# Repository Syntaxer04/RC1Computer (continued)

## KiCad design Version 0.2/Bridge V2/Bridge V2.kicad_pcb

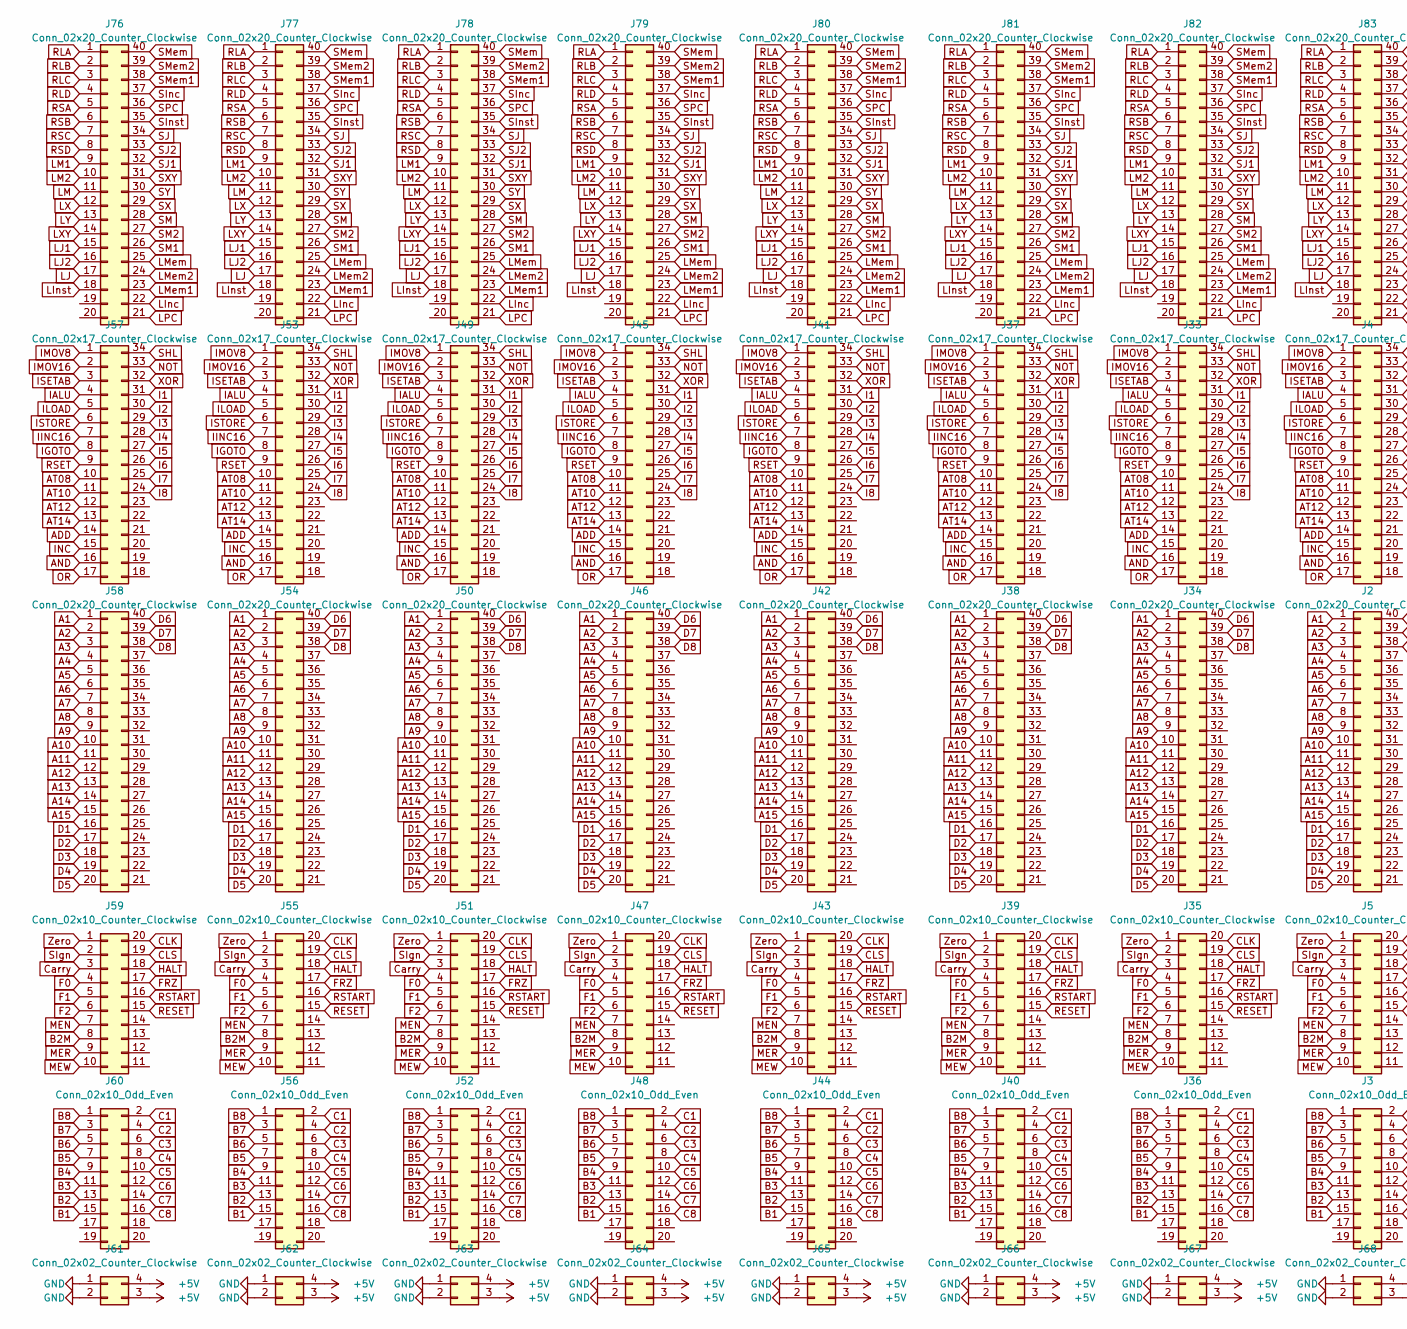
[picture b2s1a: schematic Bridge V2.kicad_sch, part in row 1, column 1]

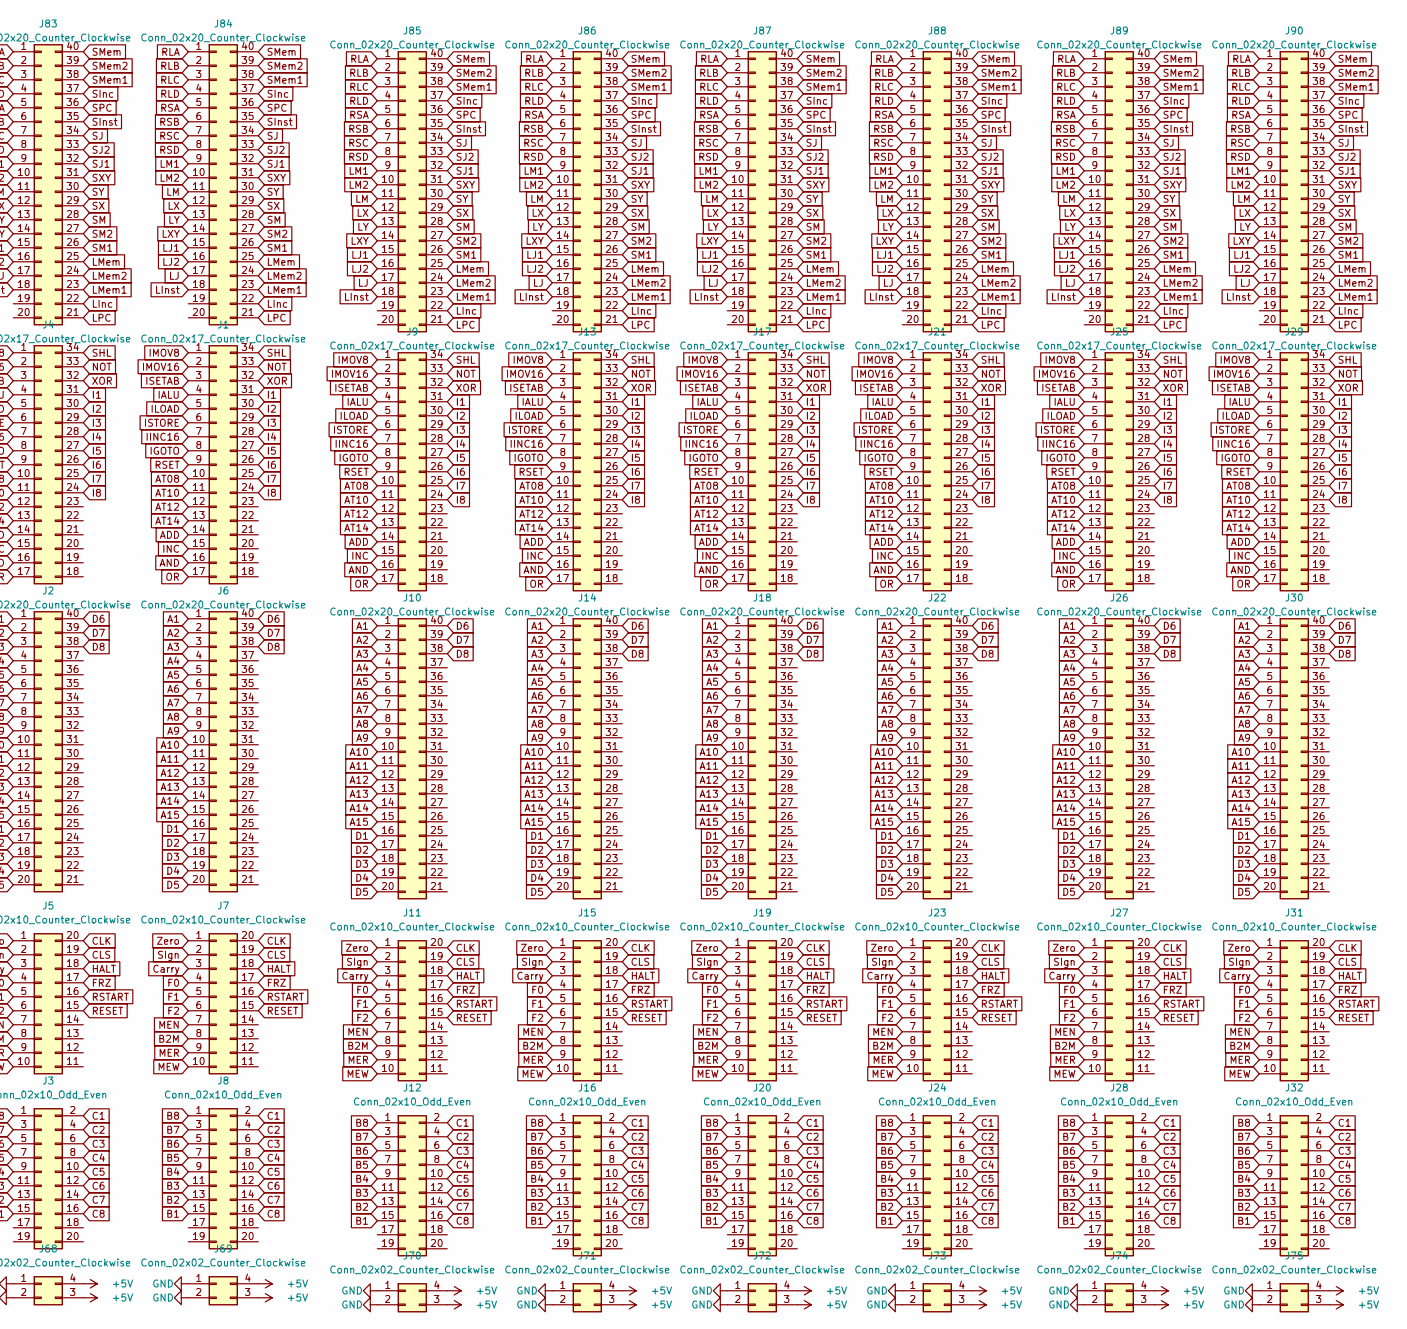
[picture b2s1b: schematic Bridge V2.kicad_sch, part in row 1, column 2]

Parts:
J1, J4, J9, J13, J17, J21, J25, J29, J33, J37, J41, J45, J49, J53, J57: Conn_02x17_Counter_Clockwise; PinSocket_2x17_P2.54mm_Vertical
J2, J6, J10, J14, J18, J22, J26, J30, J34, J38, J42, J46, J50, J54, J58, J76, J77, J78, J79, J80, J81, J82, J83, J84, J85, J86, J87, J88, J89, J90: Conn_02x20_Counter_Clockwise; PinSocket_2x20_P2.54mm_Vertical
J3, J8, J12, J16, J20, J24, J28, J32, J36, J40, J44, J48, J52, J56, J60: Conn_02x10_Odd_Even; PinSocket_2x10_P2.54mm_Vertical
J5, J7, J11, J15, J19, J23, J27, J31, J35, J39, J43, J47, J51, J55, J59: Conn_02x10_Counter_Clockwise; PinSocket_2x10_P2.54mm_Vertical
J61, J62, J63, J64, J65, J66, J67, J68, J69, J70, J71, J72, J73, J74, J75: Conn_02x02_Counter_Clockwise; PinSocket_2x02_P2.54mm_Vertical

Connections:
+5V: J61.3, J61.4, J62.3, J62.4, J63.3, J63.4, J64.3, J64.4, J65.3, J65.4, J66.3, J66.4, J67.3, J67.4, J68.3, J68.4, J69.3, J69.4, J70.3, J70.4, J71.3, J71.4, J72.3, J72.4, J73.3, J73.4, J74.3, J74.4, J75.3, J75.4
A1: J2.1, J6.1, J10.1, J14.1, J18.1, J22.1, J26.1, J30.1, J34.1, J38.1, J42.1, J46.1, J50.1, J54.1, J58.1
A2: J2.2, J6.2, J10.2, J14.2, J18.2, J22.2, J26.2, J30.2, J34.2, J38.2, J42.2, J46.2, J50.2, J54.2, J58.2
A3: J2.3, J6.3, J10.3, J14.3, J18.3, J22.3, J26.3, J30.3, J34.3, J38.3, J42.3, J46.3, J50.3, J54.3, J58.3
A4: J2.4, J6.4, J10.4, J14.4, J18.4, J22.4, J26.4, J30.4, J34.4, J38.4, J42.4, J46.4, J50.4, J54.4, J58.4
A5: J2.5, J6.5, J10.5, J14.5, J18.5, J22.5, J26.5, J30.5, J34.5, J38.5, J42.5, J46.5, J50.5, J54.5, J58.5
A6: J2.6, J6.6, J10.6, J14.6, J18.6, J22.6, J26.6, J30.6, J34.6, J38.6, J42.6, J46.6, J50.6, J54.6, J58.6
A7: J2.7, J6.7, J10.7, J14.7, J18.7, J22.7, J26.7, J30.7, J34.7, J38.7, J42.7, J46.7, J50.7, J54.7, J58.7
A8: J2.8, J6.8, J10.8, J14.8, J18.8, J22.8, J26.8, J30.8, J34.8, J38.8, J42.8, J46.8, J50.8, J54.8, J58.8
A9: J2.9, J6.9, J10.9, J14.9, J18.9, J22.9, J26.9, J30.9, J34.9, J38.9, J42.9, J46.9, J50.9, J54.9, J58.9
A10: J2.10, J6.10, J10.10, J14.10, J18.10, J22.10, J26.10, J30.10, J34.10, J38.10, J42.10, J46.10, J50.10, J54.10, J58.10
A11: J2.11, J6.11, J10.11, J14.11, J18.11, J22.11, J26.11, J30.11, J34.11, J38.11, J42.11, J46.11, J50.11, J54.11, J58.11
A12: J2.12, J6.12, J10.12, J14.12, J18.12, J22.12, J26.12, J30.12, J34.12, J38.12, J42.12, J46.12, J50.12, J54.12, J58.12
A13: J2.13, J6.13, J10.13, J14.13, J18.13, J22.13, J26.13, J30.13, J34.13, J38.13, J42.13, J46.13, J50.13, J54.13, J58.13
A14: J2.14, J6.14, J10.14, J14.14, J18.14, J22.14, J26.14, J30.14, J34.14, J38.14, J42.14, J46.14, J50.14, J54.14, J58.14
A15: J2.15, J6.15, J10.15, J14.15, J18.15, J22.15, J26.15, J30.15, J34.15, J38.15, J42.15, J46.15, J50.15, J54.15, J58.15
ADD: J1.14, J4.14, J9.14, J13.14, J17.14, J21.14, J25.14, J29.14, J33.14, J37.14, J41.14, J45.14, J49.14, J53.14, J57.14
AND: J1.16, J4.16, J9.16, J13.16, J17.16, J21.16, J25.16, J29.16, J33.16, J37.16, J41.16, J45.16, J49.16, J53.16, J57.16
AT08: J1.10, J4.10, J9.10, J13.10, J17.10, J21.10, J25.10, J29.10, J33.10, J37.10, J41.10, J45.10, J49.10, J53.10, J57.10
AT10: J1.11, J4.11, J9.11, J13.11, J17.11, J21.11, J25.11, J29.11, J33.11, J37.11, J41.11, J45.11, J49.11, J53.11, J57.11
AT12: J1.12, J4.12, J9.12, J13.12, J17.12, J21.12, J25.12, J29.12, J33.12, J37.12, J41.12, J45.12, J49.12, J53.12, J57.12
AT14: J1.13, J4.13, J9.13, J13.13, J17.13, J21.13, J25.13, J29.13, J33.13, J37.13, J41.13, J45.13, J49.13, J53.13, J57.13
B1: J3.15, J8.15, J12.15, J16.15, J20.15, J24.15, J28.15, J32.15, J36.15, J40.15, J44.15, J48.15, J52.15, J56.15, J60.15
B2: J3.13, J8.13, J12.13, J16.13, J20.13, J24.13, J28.13, J32.13, J36.13, J40.13, J44.13, J48.13, J52.13, J56.13, J60.13
B2M: J5.8, J7.8, J11.8, J15.8, J19.8, J23.8, J27.8, J31.8, J35.8, J39.8, J43.8, J47.8, J51.8, J55.8, J59.8
B3: J3.11, J8.11, J12.11, J16.11, J20.11, J24.11, J28.11, J32.11, J36.11, J40.11, J44.11, J48.11, J52.11, J56.11, J60.11
B4: J3.9, J8.9, J12.9, J16.9, J20.9, J24.9, J28.9, J32.9, J36.9, J40.9, J44.9, J48.9, J52.9, J56.9, J60.9
B5: J3.7, J8.7, J12.7, J16.7, J20.7, J24.7, J28.7, J32.7, J36.7, J40.7, J44.7, J48.7, J52.7, J56.7, J60.7
B6: J3.5, J8.5, J12.5, J16.5, J20.5, J24.5, J28.5, J32.5, J36.5, J40.5, J44.5, J48.5, J52.5, J56.5, J60.5
B7: J3.3, J8.3, J12.3, J16.3, J20.3, J24.3, J28.3, J32.3, J36.3, J40.3, J44.3, J48.3, J52.3, J56.3, J60.3
B8: J3.1, J8.1, J12.1, J16.1, J20.1, J24.1, J28.1, J32.1, J36.1, J40.1, J44.1, J48.1, J52.1, J56.1, J60.1
C1: J3.2, J8.2, J12.2, J16.2, J20.2, J24.2, J28.2, J32.2, J36.2, J40.2, J44.2, J48.2, J52.2, J56.2, J60.2
C2: J3.4, J8.4, J12.4, J16.4, J20.4, J24.4, J28.4, J32.4, J36.4, J40.4, J44.4, J48.4, J52.4, J56.4, J60.4
C3: J3.6, J8.6, J12.6, J16.6, J20.6, J24.6, J28.6, J32.6, J36.6, J40.6, J44.6, J48.6, J52.6, J56.6, J60.6
C4: J3.8, J8.8, J12.8, J16.8, J20.8, J24.8, J28.8, J32.8, J36.8, J40.8, J44.8, J48.8, J52.8, J56.8, J60.8
C5: J3.10, J8.10, J12.10, J16.10, J20.10, J24.10, J28.10, J32.10, J36.10, J40.10, J44.10, J48.10, J52.10, J56.10, J60.10
C6: J3.12, J8.12, J12.12, J16.12, J20.12, J24.12, J28.12, J32.12, J36.12, J40.12, J44.12, J48.12, J52.12, J56.12, J60.12
C7: J3.14, J8.14, J12.14, J16.14, J20.14, J24.14, J28.14, J32.14, J36.14, J40.14, J44.14, J48.14, J52.14, J56.14, J60.14
C8: J3.16, J8.16, J12.16, J16.16, J20.16, J24.16, J28.16, J32.16, J36.16, J40.16, J44.16, J48.16, J52.16, J56.16, J60.16
CLK: J5.20, J7.20, J11.20, J15.20, J19.20, J23.20, J27.20, J31.20, J35.20, J39.20, J43.20, J47.20, J51.20, J55.20, J59.20
CLS: J5.19, J7.19, J11.19, J15.19, J19.19, J23.19, J27.19, J31.19, J35.19, J39.19, J43.19, J47.19, J51.19, J55.19, J59.19
Carry: J5.3, J7.3, J11.3, J15.3, J19.3, J23.3, J27.3, J31.3, J35.3, J39.3, J43.3, J47.3, J51.3, J55.3, J59.3
D1: J2.16, J6.16, J10.16, J14.16, J18.16, J22.16, J26.16, J30.16, J34.16, J38.16, J42.16, J46.16, J50.16, J54.16, J58.16
D2: J2.17, J6.17, J10.17, J14.17, J18.17, J22.17, J26.17, J30.17, J34.17, J38.17, J42.17, J46.17, J50.17, J54.17, J58.17
D3: J2.18, J6.18, J10.18, J14.18, J18.18, J22.18, J26.18, J30.18, J34.18, J38.18, J42.18, J46.18, J50.18, J54.18, J58.18
D4: J2.19, J6.19, J10.19, J14.19, J18.19, J22.19, J26.19, J30.19, J34.19, J38.19, J42.19, J46.19, J50.19, J54.19, J58.19
D5: J2.20, J6.20, J10.20, J14.20, J18.20, J22.20, J26.20, J30.20, J34.20, J38.20, J42.20, J46.20, J50.20, J54.20, J58.20
D6: J2.40, J6.40, J10.40, J14.40, J18.40, J22.40, J26.40, J30.40, J34.40, J38.40, J42.40, J46.40, J50.40, J54.40, J58.40
D7: J2.39, J6.39, J10.39, J14.39, J18.39, J22.39, J26.39, J30.39, J34.39, J38.39, J42.39, J46.39, J50.39, J54.39, J58.39
D8: J2.38, J6.38, J10.38, J14.38, J18.38, J22.38, J26.38, J30.38, J34.38, J38.38, J42.38, J46.38, J50.38, J54.38, J58.38
F0: J5.4, J7.4, J11.4, J15.4, J19.4, J23.4, J27.4, J31.4, J35.4, J39.4, J43.4, J47.4, J51.4, J55.4, J59.4
F1: J5.5, J7.5, J11.5, J15.5, J19.5, J23.5, J27.5, J31.5, J35.5, J39.5, J43.5, J47.5, J51.5, J55.5, J59.5
F2: J5.6, J7.6, J11.6, J15.6, J19.6, J23.6, J27.6, J31.6, J35.6, J39.6, J43.6, J47.6, J51.6, J55.6, J59.6
FRZ: J5.17, J7.17, J11.17, J15.17, J19.17, J23.17, J27.17, J31.17, J35.17, J39.17, J43.17, J47.17, J51.17, J55.17, J59.17
GND: J61.1, J61.2, J62.1, J62.2, J63.1, J63.2, J64.1, J64.2, J65.1, J65.2, J66.1, J66.2, J67.1, J67.2, J68.1, J68.2, J69.1, J69.2, J70.1, J70.2, J71.1, J71.2, J72.1, J72.2, J73.1, J73.2, J74.1, J74.2, J75.1, J75.2
HALT: J5.18, J7.18, J11.18, J15.18, J19.18, J23.18, J27.18, J31.18, J35.18, J39.18, J43.18, J47.18, J51.18, J55.18, J59.18
I1: J1.31, J4.31, J9.31, J13.31, J17.31, J21.31, J25.31, J29.31, J33.31, J37.31, J41.31, J45.31, J49.31, J53.31, J57.31
I2: J1.30, J4.30, J9.30, J13.30, J17.30, J21.30, J25.30, J29.30, J33.30, J37.30, J41.30, J45.30, J49.30, J53.30, J57.30
I3: J1.29, J4.29, J9.29, J13.29, J17.29, J21.29, J25.29, J29.29, J33.29, J37.29, J41.29, J45.29, J49.29, J53.29, J57.29
I4: J1.28, J4.28, J9.28, J13.28, J17.28, J21.28, J25.28, J29.28, J33.28, J37.28, J41.28, J45.28, J49.28, J53.28, J57.28
I5: J1.27, J4.27, J9.27, J13.27, J17.27, J21.27, J25.27, J29.27, J33.27, J37.27, J41.27, J45.27, J49.27, J53.27, J57.27
I6: J1.26, J4.26, J9.26, J13.26, J17.26, J21.26, J25.26, J29.26, J33.26, J37.26, J41.26, J45.26, J49.26, J53.26, J57.26
I7: J1.25, J4.25, J9.25, J13.25, J17.25, J21.25, J25.25, J29.25, J33.25, J37.25, J41.25, J45.25, J49.25, J53.25, J57.25
I8: J1.24, J4.24, J9.24, J13.24, J17.24, J21.24, J25.24, J29.24, J33.24, J37.24, J41.24, J45.24, J49.24, J53.24, J57.24
IALU: J1.4, J4.4, J9.4, J13.4, J17.4, J21.4, J25.4, J29.4, J33.4, J37.4, J41.4, J45.4, J49.4, J53.4, J57.4
IGOTO: J1.8, J4.8, J9.8, J13.8, J17.8, J21.8, J25.8, J29.8, J33.8, J37.8, J41.8, J45.8, J49.8, J53.8, J57.8
IINC16: J1.7, J4.7, J9.7, J13.7, J17.7, J21.7, J25.7, J29.7, J33.7, J37.7, J41.7, J45.7, J49.7, J53.7, J57.7
ILOAD: J1.5, J4.5, J9.5, J13.5, J17.5, J21.5, J25.5, J29.5, J33.5, J37.5, J41.5, J45.5, J49.5, J53.5, J57.5
IMOV8: J1.1, J4.1, J9.1, J13.1, J17.1, J21.1, J25.1, J29.1, J33.1, J37.1, J41.1, J45.1, J49.1, J53.1, J57.1
IMOV16: J1.2, J4.2, J9.2, J13.2, J17.2, J21.2, J25.2, J29.2, J33.2, J37.2, J41.2, J45.2, J49.2, J53.2, J57.2
INC: J1.15, J4.15, J9.15, J13.15, J17.15, J21.15, J25.15, J29.15, J33.15, J37.15, J41.15, J45.15, J49.15, J53.15, J57.15
ISETAB: J1.3, J4.3, J9.3, J13.3, J17.3, J21.3, J25.3, J29.3, J33.3, J37.3, J41.3, J45.3, J49.3, J53.3, J57.3
ISTORE: J1.6, J4.6, J9.6, J13.6, J17.6, J21.6, J25.6, J29.6, J33.6, J37.6, J41.6, J45.6, J49.6, J53.6, J57.6
LInc: J76.22, J77.22, J78.22, J79.22, J80.22, J81.22, J82.22, J83.22, J84.22, J85.22, J86.22, J87.22, J88.22, J89.22, J90.22
LInst: J76.18, J77.18, J78.18, J79.18, J80.18, J81.18, J82.18, J83.18, J84.18, J85.18, J86.18, J87.18, J88.18, J89.18, J90.18
LJ1: J76.15, J77.15, J78.15, J79.15, J80.15, J81.15, J82.15, J83.15, J84.15, J85.15, J86.15, J87.15, J88.15, J89.15, J90.15
LJ2: J76.16, J77.16, J78.16, J79.16, J80.16, J81.16, J82.16, J83.16, J84.16, J85.16, J86.16, J87.16, J88.16, J89.16, J90.16
LJ: J76.17, J77.17, J78.17, J79.17, J80.17, J81.17, J82.17, J83.17, J84.17, J85.17, J86.17, J87.17, J88.17, J89.17, J90.17
LM: J76.11, J77.11, J78.11, J79.11, J80.11, J81.11, J82.11, J83.11, J84.11, J85.11, J86.11, J87.11, J88.11, J89.11, J90.11
LM1: J76.9, J77.9, J78.9, J79.9, J80.9, J81.9, J82.9, J83.9, J84.9, J85.9, J86.9, J87.9, J88.9, J89.9, J90.9
LM2: J76.10, J77.10, J78.10, J79.10, J80.10, J81.10, J82.10, J83.10, J84.10, J85.10, J86.10, J87.10, J88.10, J89.10, J90.10
LMem: J76.25, J77.25, J78.25, J79.25, J80.25, J81.25, J82.25, J83.25, J84.25, J85.25, J86.25, J87.25, J88.25, J89.25, J90.25
LMem1: J76.23, J77.23, J78.23, J79.23, J80.23, J81.23, J82.23, J83.23, J84.23, J85.23, J86.23, J87.23, J88.23, J89.23, J90.23
LMem2: J76.24, J77.24, J78.24, J79.24, J80.24, J81.24, J82.24, J83.24, J84.24, J85.24, J86.24, J87.24, J88.24, J89.24, J90.24
LPC: J76.21, J77.21, J78.21, J79.21, J80.21, J81.21, J82.21, J83.21, J84.21, J85.21, J86.21, J87.21, J88.21, J89.21, J90.21
LX: J76.12, J77.12, J78.12, J79.12, J80.12, J81.12, J82.12, J83.12, J84.12, J85.12, J86.12, J87.12, J88.12, J89.12, J90.12
LXY: J76.14, J77.14, J78.14, J79.14, J80.14, J81.14, J82.14, J83.14, J84.14, J85.14, J86.14, J87.14, J88.14, J89.14, J90.14
LY: J76.13, J77.13, J78.13, J79.13, J80.13, J81.13, J82.13, J83.13, J84.13, J85.13, J86.13, J87.13, J88.13, J89.13, J90.13
MEN: J5.7, J7.7, J11.7, J15.7, J19.7, J23.7, J27.7, J31.7, J35.7, J39.7, J43.7, J47.7, J51.7, J55.7, J59.7
MER: J5.9, J7.9, J11.9, J15.9, J19.9, J23.9, J27.9, J31.9, J35.9, J39.9, J43.9, J47.9, J51.9, J55.9, J59.9
MEW: J5.10, J7.10, J11.10, J15.10, J19.10, J23.10, J27.10, J31.10, J35.10, J39.10, J43.10, J47.10, J51.10, J55.10, J59.10
NOT: J1.33, J4.33, J9.33, J13.33, J17.33, J21.33, J25.33, J29.33, J33.33, J37.33, J41.33, J45.33, J49.33, J53.33, J57.33
OR: J1.17, J4.17, J9.17, J13.17, J17.17, J21.17, J25.17, J29.17, J33.17, J37.17, J41.17, J45.17, J49.17, J53.17, J57.17
RESET: J5.15, J7.15, J11.15, J15.15, J19.15, J23.15, J27.15, J31.15, J35.15, J39.15, J43.15, J47.15, J51.15, J55.15, J59.15
RLA: J76.1, J77.1, J78.1, J79.1, J80.1, J81.1, J82.1, J83.1, J84.1, J85.1, J86.1, J87.1, J88.1, J89.1, J90.1
RLB: J76.2, J77.2, J78.2, J79.2, J80.2, J81.2, J82.2, J83.2, J84.2, J85.2, J86.2, J87.2, J88.2, J89.2, J90.2
RLC: J76.3, J77.3, J78.3, J79.3, J80.3, J81.3, J82.3, J83.3, J84.3, J85.3, J86.3, J87.3, J88.3, J89.3, J90.3
RLD: J76.4, J77.4, J78.4, J79.4, J80.4, J81.4, J82.4, J83.4, J84.4, J85.4, J86.4, J87.4, J88.4, J89.4, J90.4
RSA: J76.5, J77.5, J78.5, J79.5, J80.5, J81.5, J82.5, J83.5, J84.5, J85.5, J86.5, J87.5, J88.5, J89.5, J90.5
RSB: J76.6, J77.6, J78.6, J79.6, J80.6, J81.6, J82.6, J83.6, J84.6, J85.6, J86.6, J87.6, J88.6, J89.6, J90.6
RSC: J76.7, J77.7, J78.7, J79.7, J80.7, J81.7, J82.7, J83.7, J84.7, J85.7, J86.7, J87.7, J88.7, J89.7, J90.7
RSD: J76.8, J77.8, J78.8, J79.8, J80.8, J81.8, J82.8, J83.8, J84.8, J85.8, J86.8, J87.8, J88.8, J89.8, J90.8
RSET: J1.9, J4.9, J9.9, J13.9, J17.9, J21.9, J25.9, J29.9, J33.9, J37.9, J41.9, J45.9, J49.9, J53.9, J57.9
RSTART: J5.16, J7.16, J11.16, J15.16, J19.16, J23.16, J27.16, J31.16, J35.16, J39.16, J43.16, J47.16, J51.16, J55.16, J59.16
SHL: J1.34, J4.34, J9.34, J13.34, J17.34, J21.34, J25.34, J29.34, J33.34, J37.34, J41.34, J45.34, J49.34, J53.34, J57.34
SIgn: J5.2, J7.2, J11.2, J15.2, J19.2, J23.2, J27.2, J31.2, J35.2, J39.2, J43.2, J47.2, J51.2, J55.2, J59.2
SInc: J76.37, J77.37, J78.37, J79.37, J80.37, J81.37, J82.37, J83.37, J84.37, J85.37, J86.37, J87.37, J88.37, J89.37, J90.37
SInst: J76.35, J77.35, J78.35, J79.35, J80.35, J81.35, J82.35, J83.35, J84.35, J85.35, J86.35, J87.35, J88.35, J89.35, J90.35
SJ1: J76.32, J77.32, J78.32, J79.32, J80.32, J81.32, J82.32, J83.32, J84.32, J85.32, J86.32, J87.32, J88.32, J89.32, J90.32
SJ2: J76.33, J77.33, J78.33, J79.33, J80.33, J81.33, J82.33, J83.33, J84.33, J85.33, J86.33, J87.33, J88.33, J89.33, J90.33
SJ: J76.34, J77.34, J78.34, J79.34, J80.34, J81.34, J82.34, J83.34, J84.34, J85.34, J86.34, J87.34, J88.34, J89.34, J90.34
SM: J76.28, J77.28, J78.28, J79.28, J80.28, J81.28, J82.28, J83.28, J84.28, J85.28, J86.28, J87.28, J88.28, J89.28, J90.28
SM1: J76.26, J77.26, J78.26, J79.26, J80.26, J81.26, J82.26, J83.26, J84.26, J85.26, J86.26, J87.26, J88.26, J89.26, J90.26
SM2: J76.27, J77.27, J78.27, J79.27, J80.27, J81.27, J82.27, J83.27, J84.27, J85.27, J86.27, J87.27, J88.27, J89.27, J90.27
SMem: J76.40, J77.40, J78.40, J79.40, J80.40, J81.40, J82.40, J83.40, J84.40, J85.40, J86.40, J87.40, J88.40, J89.40, J90.40
SMem1: J76.38, J77.38, J78.38, J79.38, J80.38, J81.38, J82.38, J83.38, J84.38, J85.38, J86.38, J87.38, J88.38, J89.38, J90.38
SMem2: J76.39, J77.39, J78.39, J79.39, J80.39, J81.39, J82.39, J83.39, J84.39, J85.39, J86.39, J87.39, J88.39, J89.39, J90.39
SPC: J76.36, J77.36, J78.36, J79.36, J80.36, J81.36, J82.36, J83.36, J84.36, J85.36, J86.36, J87.36, J88.36, J89.36, J90.36
SX: J76.29, J77.29, J78.29, J79.29, J80.29, J81.29, J82.29, J83.29, J84.29, J85.29, J86.29, J87.29, J88.29, J89.29, J90.29
SXY: J76.31, J77.31, J78.31, J79.31, J80.31, J81.31, J82.31, J83.31, J84.31, J85.31, J86.31, J87.31, J88.31, J89.31, J90.31
SY: J76.30, J77.30, J78.30, J79.30, J80.30, J81.30, J82.30, J83.30, J84.30, J85.30, J86.30, J87.30, J88.30, J89.30, J90.30
XOR: J1.32, J4.32, J9.32, J13.32, J17.32, J21.32, J25.32, J29.32, J33.32, J37.32, J41.32, J45.32, J49.32, J53.32, J57.32
Zero: J5.1, J7.1, J11.1, J15.1, J19.1, J23.1, J27.1, J31.1, J35.1, J39.1, J43.1, J47.1, J51.1, J55.1, J59.1

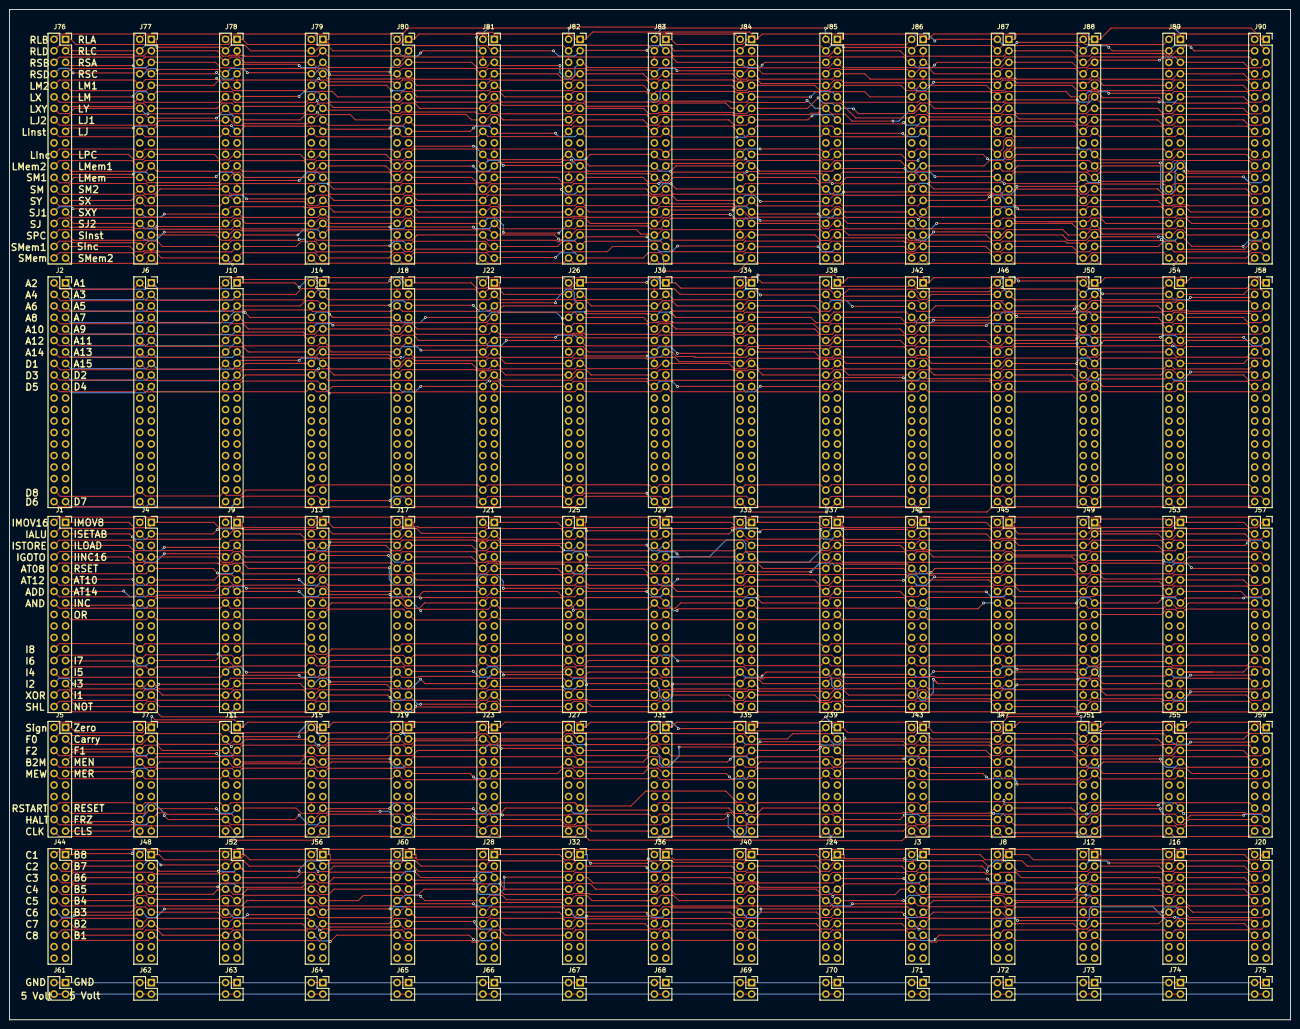
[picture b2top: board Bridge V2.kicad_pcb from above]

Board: 2 copper layers, 282.7 x 222.9 mm, 90 parts (0 on the bottom side), 123 nets.

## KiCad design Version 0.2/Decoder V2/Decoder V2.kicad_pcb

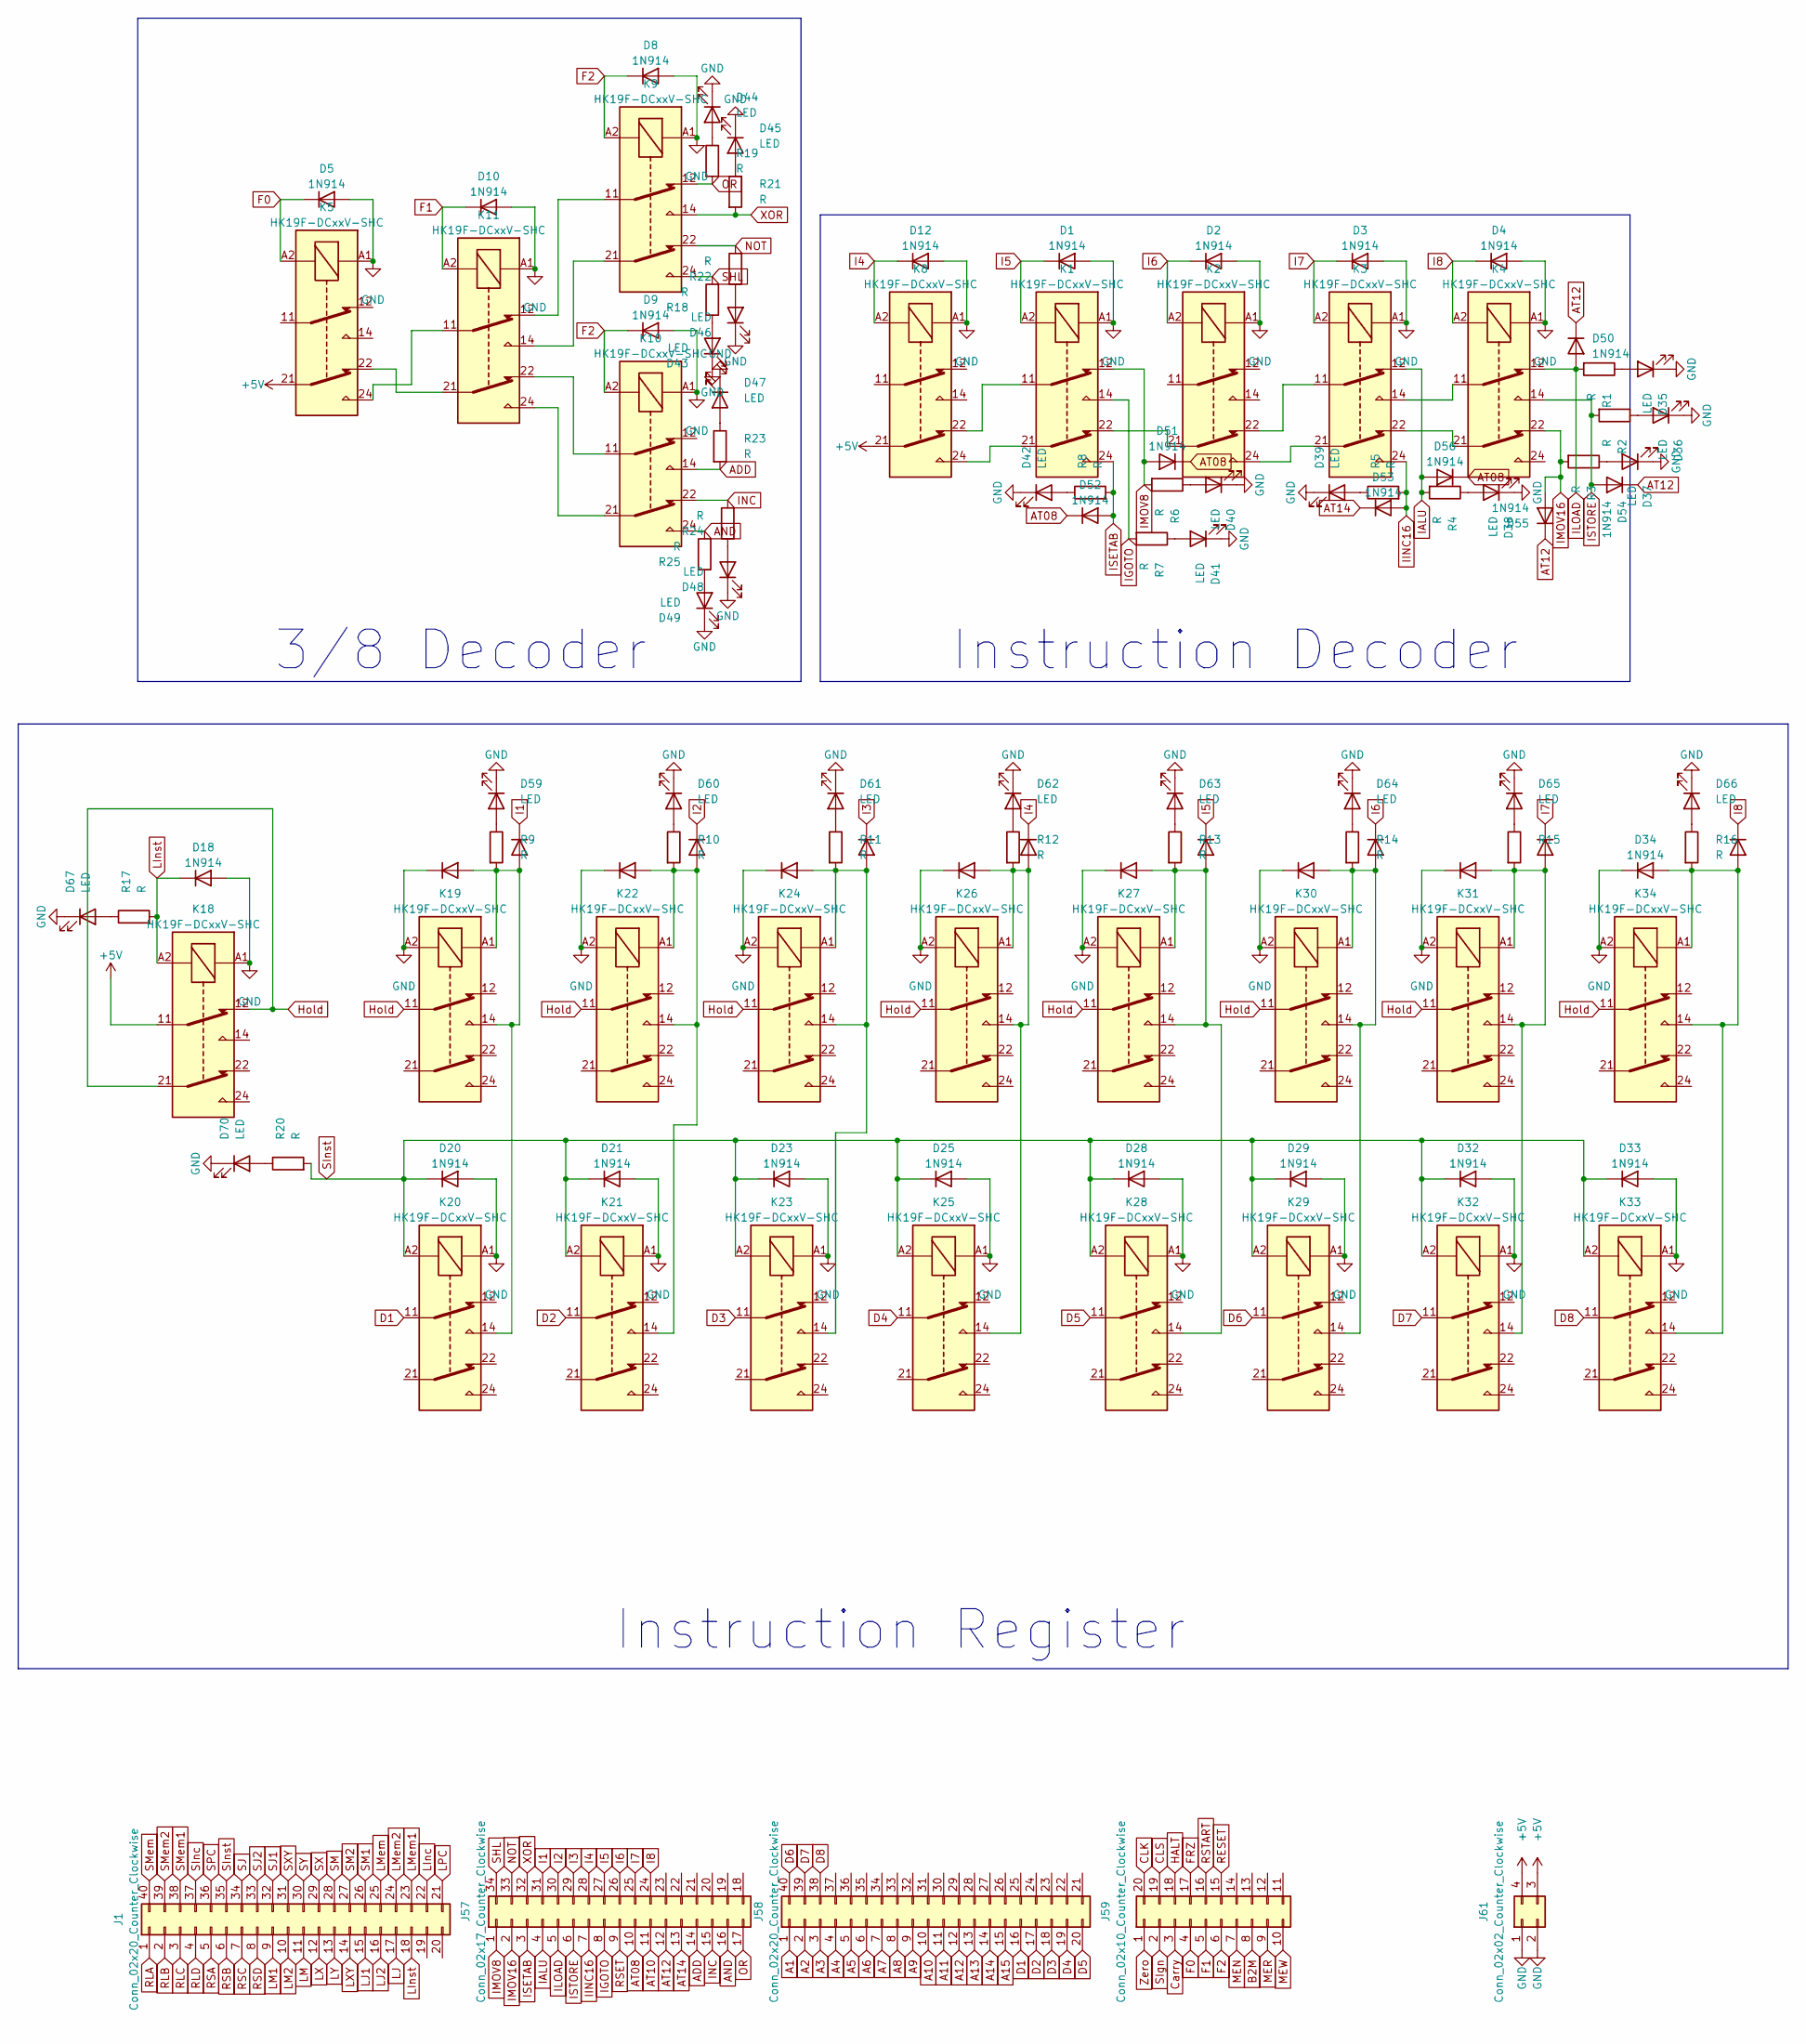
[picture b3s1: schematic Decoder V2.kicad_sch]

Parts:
D1, D2, D3, D4, D5, D6, D7, D8, D9, D10, D11, D12, D13, D14, D15, D16, D17, D18, D19, D20, D21, D22, D23, D24, D25, D26, D27, D28, D29, D30, D31, D32, D33, D34, D50, D51, D52, D53, D54, D55, D56: 1N914; D_DO-35_SOD27_P7.62mm_Horizontal
D35, D36, D37, D38, D39, D40, D41, D42, D43, D44, D45, D46, D47, D48, D49, D59, D60, D61, D62, D63, D64, D65, D66, D67, D70: LED; LED_D5.0mm ohne SilkS
J1, J58: Conn_02x20_Counter_Clockwise; PinSocket_2x20_P2.54mm_Horizontal
J57: Conn_02x17_Counter_Clockwise; PinSocket_2x17_P2.54mm_Horizontal
J59: Conn_02x10_Counter_Clockwise; PinSocket_2x10_P2.54mm_Horizontal
J61: Conn_02x02_Counter_Clockwise; PinSocket_2x02_P2.54mm_Horizontal
K1, K2, K3, K4, K5, K8, K9, K10, K11, K18, K19, K20, K21, K22, K23, K24, K25, K26, K27, K28, K29, K30, K31, K32, K33, K34: HK19F-DCxxV-SHC; Relay_DPDT_Finder_30.22 ohne SilkS
R1, R2, R3, R4, R5, R6, R7, R8, R9, R10, R11, R12, R13, R14, R15, R16, R17, R18, R19, R20, R21, R22, R23, R24, R25: R; R_Axial_DIN0204_L3.6mm_D1.6mm_P7.62mm_Horizontal

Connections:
+5V: J61.3, J61.4, K5.21, K8.21, K18.11
A1: J58.1
A2: J58.2
A3: J58.3
A4: J58.4
A5: J58.5
A6: J58.6
A7: J58.7
A8: J58.8
A9: J58.9
A10: J58.10
A11: J58.11
A12: J58.12
A13: J58.13
A14: J58.14
A15: J58.15
ADD: J57.14, K10.14, R23.2
AND: J57.16, K10.24, R25.2
AT08: D51.1 (K), D52.1 (K), D56.1 (K), J57.10
AT10: J57.11
AT12: D50.1 (K), D54.1 (K), D55.1 (K), J57.12
AT14: D53.1 (K), J57.13
B2M: J59.8
CLK: J59.20
CLS: J59.19
Carry: J59.3
D1: J58.16, K20.11
D2: J58.17, K21.11
D3: J58.18, K23.11
D4: J58.19, K25.11
D5: J58.20, K28.11
D6: J58.40, K29.11
D7: J58.39, K32.11
D8: J58.38, K33.11
F0: D5.1 (K), J59.4, K5.A2
F1: D10.1 (K), J59.5, K11.A2
F2: D8.1 (K), D9.1 (K), J59.6, K9.A2, K10.A2
FRZ: J59.17
GND: D1.2 (A), D2.2 (A), D3.2 (A), D4.2 (A), D5.2 (A), D8.2 (A), D9.2 (A), D10.2 (A), D12.2 (A), D18.2 (A), D19.1 (K), D20.2 (A), D21.2 (A), D22.1 (K), D23.2 (A), D24.1 (K), D25.2 (A), D26.1 (K), D27.1 (K), D28.2 (A), D29.2 (A), D30.1 (K), D31.1 (K), D32.2 (A), D33.2 (A), D34.1 (K), D35.1 (K), D36.1 (K), D37.1 (K), D38.1 (K), D39.1 (K), D40.1 (K), D41.1 (K), D42.1 (K), D43.1 (K), D44.1 (K), D45.1 (K), D46.1 (K), D47.1 (K), D48.1 (K), D49.1 (K), D59.1 (K), D60.1 (K), D61.1 (K), D62.1 (K), D63.1 (K), D64.1 (K), D65.1 (K), D66.1 (K), D67.1 (K), D70.1 (K), J61.1, J61.2, K1.A1, K2.A1, K3.A1, K4.A1, K5.A1, K8.A1, K9.A1, K10.A1, K11.A1, K18.A1, K19.A2, K20.A1, K21.A1, K22.A2, K23.A1, K24.A2, K25.A1, K26.A2, K27.A2, K28.A1, K29.A1, K30.A2, K31.A2, K32.A1, K33.A1, K34.A2
HALT: J59.18
Hold: K18.12, K18.21, K19.11, K22.11, K24.11, K26.11, K27.11, K30.11, K31.11, K34.11
I1: D17.1 (K), J57.31
I2: D16.1 (K), J57.30
I3: D15.1 (K), J57.29
I4: D12.1 (K), D14.1 (K), J57.28, K8.A2
I5: D1.1 (K), D13.1 (K), J57.27, K1.A2
I6: D2.1 (K), D11.1 (K), J57.26, K2.A2
I7: D3.1 (K), D7.1 (K), J57.25, K3.A2
I8: D4.1 (K), D6.1 (K), J57.24, K4.A2
IALU: D56.2 (A), J57.4, K3.12, R4.2
IGOTO: J57.8, K1.14, R7.2
IINC16: D53.2 (A), J57.7, K3.24, R5.2
ILOAD: D50.2 (A), J57.5, K4.12, R1.2
IMOV8: D51.2 (A), J57.1, K1.12, R6.2
IMOV16: D55.2 (A), J57.2, K4.22, R3.2
INC: J57.15, K10.22, R24.2
ISETAB: D52.2 (A), J57.3, K1.24, R8.2
ISTORE: D54.2 (A), J57.6, K4.14, R2.2
LInc: J1.22
LInst: D18.1 (K), J1.18, K18.A2, R17.2
LJ1: J1.15
LJ2: J1.16
LJ: J1.17
LM: J1.11
LM1: J1.9
LM2: J1.10
LMem: J1.25
LMem1: J1.23
LMem2: J1.24
LPC: J1.21
LX: J1.12
LXY: J1.14
LY: J1.13
MEN: J59.7
MER: J59.9
MEW: J59.10
NOT: J57.33, K9.22, R22.2
unnamed: D11.2 (A), D30.2 (A), K29.14, K30.14, K30.A1, R14.2
unnamed: D13.2 (A), D27.2 (A), K27.14, K27.A1, K28.14, R13.2
unnamed: D14.2 (A), D26.2 (A), K25.14, K26.14, K26.A1, R12.2
unnamed: D15.2 (A), D24.2 (A), K23.14, K24.14, K24.A1, R11.2
unnamed: D16.2 (A), D22.2 (A), K21.14, K22.14, K22.A1, R10.2
unnamed: D17.2 (A), D19.2 (A), K19.14, K19.A1, K20.14, R9.2
unnamed: D7.2 (A), D31.2 (A), K31.14, K31.A1, K32.14, R15.2
unnamed: D6.2 (A), D34.2 (A), K33.14, K34.14, K34.A1, R16.2
unnamed: D35.2 (A), R1.1
unnamed: D36.2 (A), R2.1
unnamed: D37.2 (A), R3.1
unnamed: D38.2 (A), R4.1
unnamed: D39.2 (A), R5.1
unnamed: D40.2 (A), R6.1
unnamed: D41.2 (A), R7.1
unnamed: D42.2 (A), R8.1
unnamed: D43.2 (A), R18.1
unnamed: D44.2 (A), R19.1
unnamed: D45.2 (A), R21.1
unnamed: D46.2 (A), R22.1
unnamed: D47.2 (A), R23.1
unnamed: D48.2 (A), R24.1
unnamed: D49.2 (A), R25.1
unnamed: D59.2 (A), R9.1
unnamed: D60.2 (A), R10.1
unnamed: D61.2 (A), R11.1
unnamed: D62.2 (A), R12.1
unnamed: D63.2 (A), R13.1
unnamed: D64.2 (A), R14.1
unnamed: D65.2 (A), R15.1
unnamed: D66.2 (A), R16.1
unnamed: D67.2 (A), R17.1
unnamed: D70.2 (A), R20.1
unnamed: K1.11, K8.22
unnamed: K1.21, K8.24
unnamed: K1.22, K2.21
unnamed: K2.22, K3.11
unnamed: K2.24, K3.21
unnamed: K3.14, K4.11
unnamed: K3.22, K4.21
unnamed: K10.11, K11.22
unnamed: K10.21, K11.24
unnamed: K5.24, K11.11
unnamed: K9.11, K11.12
unnamed: K9.21, K11.14
unnamed: K5.22, K11.21
OR: J57.17, K9.12, R19.2
RESET: J59.15
RLA: J1.1
RLB: J1.2
RLC: J1.3
RLD: J1.4
RSA: J1.5
RSB: J1.6
RSC: J1.7
RSD: J1.8
RSET: J57.9
RSTART: J59.16
SHL: J57.34, K9.24, R18.2
SIgn: J59.2
SInc: J1.37
SInst: D20.1 (K), D21.1 (K), D23.1 (K), D25.1 (K), D28.1 (K), D29.1 (K), D32.1 (K), D33.1 (K), J1.35, K20.A2, K21.A2, K23.A2, K25.A2, K28.A2, K29.A2, K32.A2, K33.A2, R20.2
SJ1: J1.32
SJ2: J1.33
SJ: J1.34
SM: J1.28
SM1: J1.26
SM2: J1.27
SMem: J1.40
SMem1: J1.38
SMem2: J1.39
SPC: J1.36
SX: J1.29
SXY: J1.31
SY: J1.30
XOR: J57.32, K9.14, R21.2
Zero: J59.1

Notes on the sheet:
Instruction Register
Instruction Decoder
3/8 Decoder
